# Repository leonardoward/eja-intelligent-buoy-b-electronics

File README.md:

# EJA Intelligent Buoy B with Ethernet - Electronic Design

Buoy B V2.0 integrates 4 main components (ESP32, LoRa, GPS and an Ethernet interface). It is a version of the previous Buoy B V1.0 but replaces the motor drivers with an Ethernet module.

This repository contains the KiCad design for the PCB of the Intelligent Buoy B. It also contains the 3D models used to visualize the design in the KiCad 3D viewer.

## Main Components ##

- [ESP32-DEVKITC-32D](https://www.digikey.com/product-detail/es/espressif-systems/ESP32-DEVKITC-32D/1965-1000-ND/9356990)
- [RFM95W LoRa Radio](https://www.digikey.com/product-detail/es/adafruit-industries-llc/3072/1528-1667-ND/6005357)
- [TB6612FNG MOTOR DRIVER BOARD](https://www.digikey.com/product-detail/es/sparkfun-electronics/ROB-14450/1568-1755-ND/7915576)
- [Adafruit Ethernet FeatherWing](https://www.digikey.com/en/products/detail/adafruit-industries-llc/3201/6165788)

## Schematic ##

<!-- [For a detailed explanation of the schematic visit the following log.](https://hackaday.io/project/173457/log/181832-buoy-b-v10-schematic-and-pcb-design) -->

## PCB Layout ##

## Assembly ##

Components List:

1. [ESP32-DEVKITC-32D](https://www.digikey.com/product-detail/es/espressif-systems/ESP32-DEVKITC-32D/1965-1000-ND/9356990)
2. [ETHERNET FEATHERWING](https://www.digikey.com/en/products/detail/adafruit-industries-llc/3201/6165788)
3. [CONN HDR 19POS 0.1 TIN PCB](https://www.digikey.com/product-detail/es/sullins-connector-solutions/PPTC191LFBN-RC/S7017-ND/810157)
4. [CONN HDR 9POS 0.1 GOLD PCB](https://www.digikey.com/product-detail/es/sullins-connector-solutions/PPPC091LFBN-RC/S7042-ND/810181)
5. [CONN HDR 9POS 0.1 GOLD PCB](https://www.digikey.com/product-detail/es/sullins-connector-solutions/PPPC091LFBN-RC/S7042-ND/810181)
8. PCB Buoy B V1.0
9. [CONN HDR 19POS 0.1 TIN PCB](https://www.digikey.com/product-detail/es/sullins-connector-solutions/PPTC191LFBN-RC/S7017-ND/810157)
10. [TERM BLK 2P SIDE ENT 5.08MM PCB](https://www.digikey.com/product-detail/es/on-shore-technology-inc/OSTTC022162/ED2609-ND/614558)
12. [CONN HDR 6POS 0.1 TIN PCB](https://www.digikey.com/product-detail/es/sullins-connector-solutions/PPTC061LFBN-RC/S7004-ND/810145)
13. [CONN HDR 5POS 0.1 GOLD PCB](https://www.digikey.com/product-detail/es/sullins-connector-solutions/PPTC051LFBN-RC/S6103-ND/807239)
14. [CONN HEADER VERT 3POS 2.54MM](https://www.digikey.com/product-detail/es/jst-sales-america-inc/S2B-XH-A-1-LF-SN/455-4226-ND/9961922)
15. [CONN HEADER VERT 3POS 2.54MM](https://www.digikey.com/product-detail/es/jst-sales-america-inc/S2B-XH-A-1-LF-SN/455-4226-ND/9961922)
16. [CONN HEADER R/A 3POS 2.5MM](https://www.digikey.com/product-detail/es/jst-sales-america-inc/S3B-XH-A-1-LF-SN/455-2954-ND/1556255)
17. Coin cell holder (included in [Adafruit Ultimate GPS](https://www.digikey.com/product-detail/es/adafruit-industries-llc/746/1528-1153-ND/5353613))
18. [Adafruit Ultimate GPS](https://www.digikey.com/product-detail/es/adafruit-industries-llc/746/1528-1153-ND/5353613)
19. CONN HDR 16POS 0.1 TIN PCB (included in [Adafruit Ultimate GPS](https://www.digikey.com/product-detail/es/adafruit-industries-llc/746/1528-1153-ND/5353613))
20. [RFM95W LoRa Radio](https://www.digikey.com/product-detail/es/adafruit-industries-llc/3072/1528-1667-ND/6005357)
21. CONN HEADER VERT 16POS 2.54MM (included in [RFM95W LoRa Radio](https://www.digikey.com/product-detail/es/adafruit-industries-llc/3072/1528-1667-ND/6005357))

<!-- [For a detailed Bill of Materials visit the following log.](https://hackaday.io/project/173457/log/183762-buoy-b-v10-bill-of-materials)

[For a detailed explanation about the soldering and assembly procedure visit the following log.](https://hackaday.io/project/173457/log/183666-buoy-b-v10-assembly) -->

<!-- ## Wiring Diagrams ##

### Battery Management ###

The original design of the board considered the following components:

- Battery (5V < Voltage < 15V)
- PCB Board Buoy B V1.0
- Buck Converter
- Switch
- Extra capacitor

Also, there is an alternative for the battery management, is possible to provide the required voltages with a boost converter and a 3.7V Battery, like the following example:

- 3.7V 1 Cell Battery
- PCB Board Buoy B V1.0
- Boost Converter
- Micro USB Breakout Board
- Switch
- Extra capacitor
- JST-XH 2 Pos female connector and a JST-XH 2 Pos male connector
- 5V Charger (only used to charge the battery)

This alternative is valid and possible, but is not ideal for longer working time (compared to the first one). It is important to consider the efficiency of the boost converter. The selected boost converter will have a voltage drop at a current higher than 500mA, that should be taken into consideration.

### Motors ###

The board was designed to handle 3 different types of motors, those are:

- Servo Motor

- Stepper Motor (using the driver TB6612FNG)

- DC Motor (using the driver TB6612FNG)

[For more information about the wiring diagrams and the project visit the following log.](https://hackaday.io/project/173457/log/182722-buoy-b-v10-wiring-diagrams)

## Future improvements ##

[For more information about the recommended future improvements for the electronic design visit the following log.](https://hackaday.io/project/173457/log/183807-future-improvements-pcb-design) -->

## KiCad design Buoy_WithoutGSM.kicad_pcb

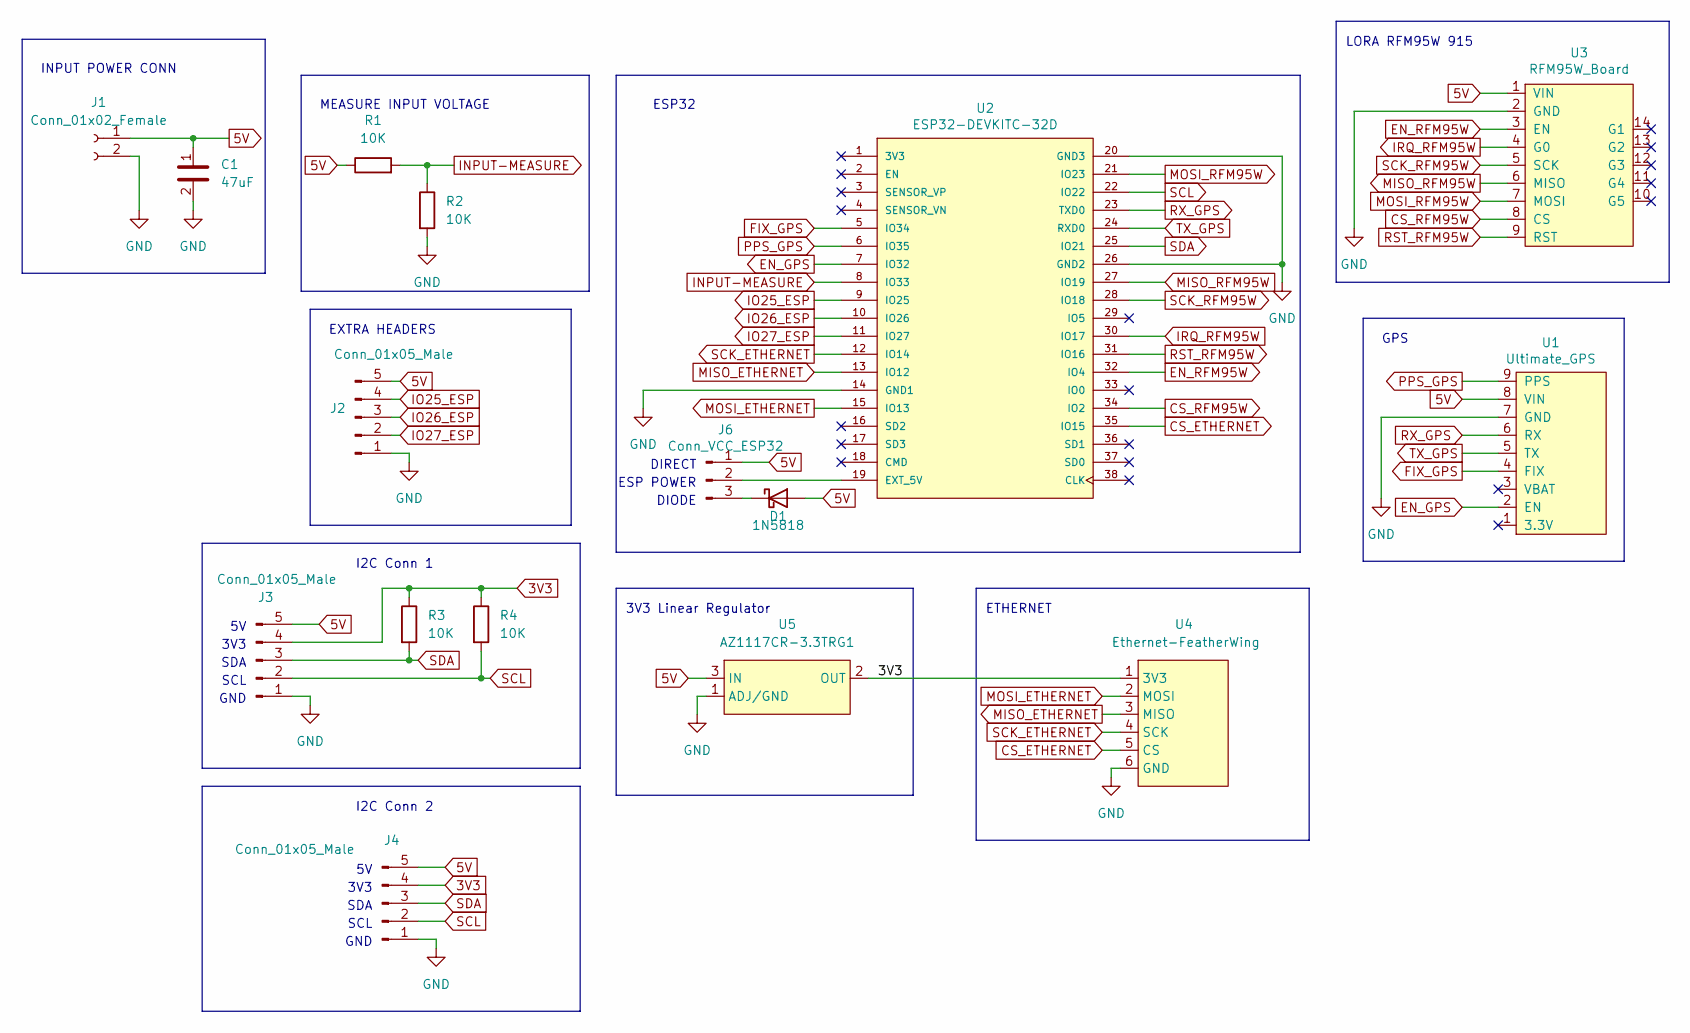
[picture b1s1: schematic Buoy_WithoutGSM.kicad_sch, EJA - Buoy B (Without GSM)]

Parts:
C1: 47uF; R_0805_2012Metric_Pad1.20x1.40mm_HandSolder; Manufacturer_Part_Number LMK212BBJ476MG-T
D1: 1N5818; D_DO-41_SOD81_P10.16mm_Horizontal
J1: Conn_01x02_Female; TerminalBlock_bornier-2_P5.08mm
J2, J3, J4: Conn_01x05_Male; PinSocket_1x05_P2.54mm_Vertical
J6: Conn_VCC_ESP32; PinHeader_1x03_P2.54mm_Vertical
R1, R2, R3, R4: 10K; R_0805_2012Metric; Manufacturer_Part_Number CRCW080510K0FKEAC
U1: Ultimate_GPS
U2: ESP32-DEVKITC-32D; MODULE_ESP32-DEVKITC-32D
U3: RFM95W_Board; RFM95W-Board
U4: Ethernet-FeatherWing; Ethernet FeatherWing; Manufacturer Part Number 3201
U5: AZ1117CR-3.3TRG1; SOT-89-3_Handsoldering; Manufacturer_Part_Name AZ1117CR-3.3TRG1

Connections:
3V3: J3.4, J4.4, R3.1, R4.1, U4.1 (3V3), U5.2 (OUT)
5V: C1.1, D1.2 (A), J1.1, J2.5, J3.5, J4.5, J6.1, R1.1, U1.8 (VIN), U3.1 (VIN), U5.3 (IN)
CS_ETHERNET: U2.35 (IO15), U4.5 (CS)
CS_RFM95W: U2.34 (IO2), U3.8 (CS)
EN_GPS: U1.2 (EN), U2.7 (IO32)
EN_RFM95W: U2.32 (IO4), U3.3 (EN)
FIX_GPS: U1.4 (FIX), U2.5 (IO34)
GND: C1.2, J1.2, J2.1, J3.1, J4.1, R2.2, U1.7 (GND), U2.14 (GND1), U2.20 (GND3), U2.26 (GND2), U3.2 (GND), U4.6 (GND), U5.1 (ADJ/GND)
INPUT-MEASURE: R1.2, R2.1, U2.8 (IO33)
IO25_ESP: J2.4, U2.9 (IO25)
IO26_ESP: J2.3, U2.10 (IO26)
IO27_ESP: J2.2, U2.11 (IO27)
IRQ_RFM95W: U2.30 (IO17), U3.4 (G0)
MISO_ETHERNET: U2.13 (IO12), U4.3 (MISO)
MISO_RFM95W: U2.27 (IO19), U3.6 (MISO)
MOSI_ETHERNET: U2.15 (IO13), U4.2 (MOSI)
MOSI_RFM95W: U2.21 (IO23), U3.7 (MOSI)
unnamed: D1.1 (K), J6.3
unnamed: J6.2, U2.19 (EXT_5V)
PPS_GPS: U1.9 (PPS), U2.6 (IO35)
RST_RFM95W: U2.31 (IO16), U3.9 (RST)
RX_GPS: U1.6 (RX), U2.23 (TXD0)
SCK_ETHERNET: U2.12 (IO14), U4.4 (SCK)
SCK_RFM95W: U2.28 (IO18), U3.5 (SCK)
SCL: J3.2, J4.2, R4.2, U2.22 (IO22)
SDA: J3.3, J4.3, R3.2, U2.25 (IO21)
TX_GPS: U1.5 (TX), U2.24 (RXD0)

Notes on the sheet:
3V3
GPS
SCL
DIODE
I2C Conn 2
MEASURE INPUT VOLTAGE
LORA RFM95W 915
ESP32
GND
ETHERNET
I2C Conn 1
ESP POWER
DIRECT
SDA
3V3 Linear Regulator
INPUT POWER CONN
EXTRA HEADERS

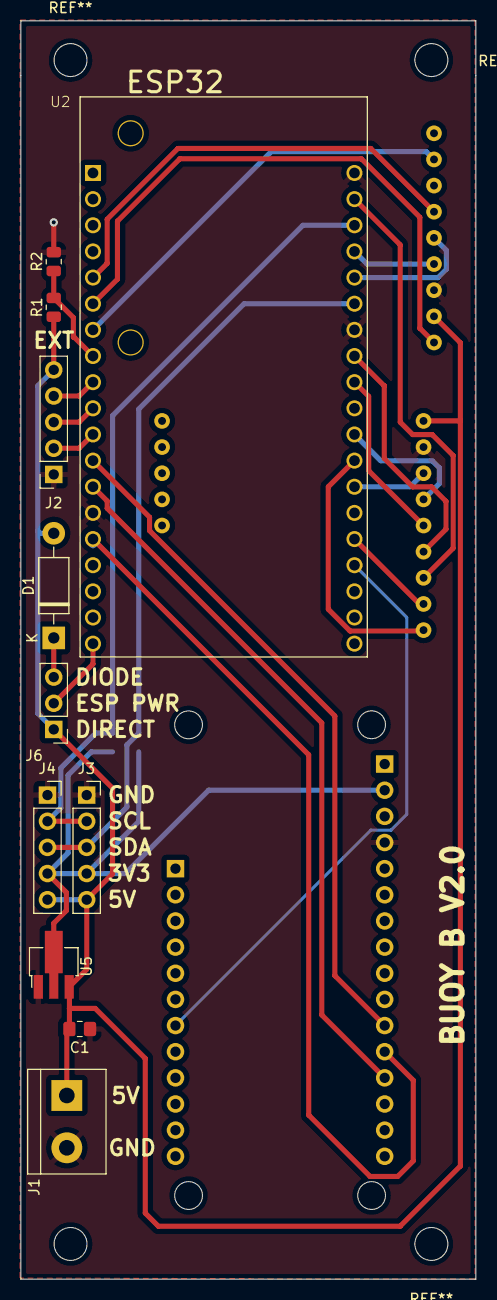
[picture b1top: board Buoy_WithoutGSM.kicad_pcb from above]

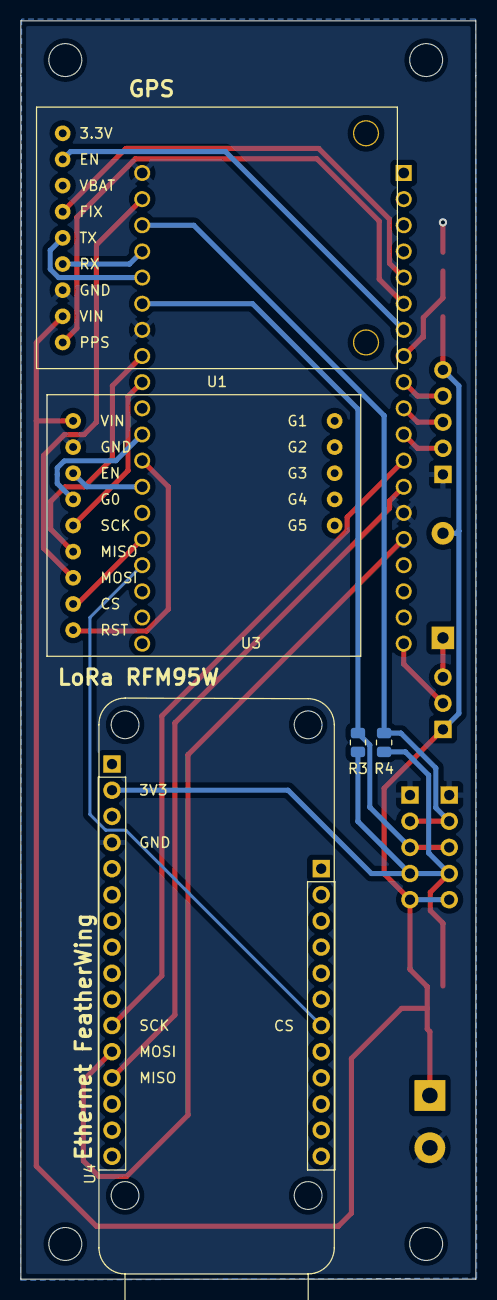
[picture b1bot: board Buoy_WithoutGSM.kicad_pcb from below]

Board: 2 copper layers, 44.2 x 122.2 mm, 16 parts (4 on the bottom side), 27 nets.

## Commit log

2020-09-28 Added KiCad design
2020-09-28 Added assembly guide and wiring diagrams
2020-09-28 Added new assembly image
2020-09-28 Fixed missing images
2020-09-28 Added components list
2020-09-28 Added links to hackaday page
2020-09-28 Fixed link to boost converter image
2020-09-28 Added future improvements
2022-08-14 Added new branch
2022-08-16 Update before modifications
2022-08-16 Updated schematic to Kicad6, removed motor diver and JST Battery connector
2022-08-16 Added Ethernet module and input measurement
2022-08-16 Added connections to the Extra Conn
2022-08-18 Added 3D model for the Ethernet module and routed changes on PCB
2022-08-19 Updated readme, added new images
2022-09-02 Changed toutes of the PCB, including routes width
2022-09-09 Updated documentation
2022-09-09 Added gerber files
2022-09-23 Moved C1 on the PCB, changed PCB shape, moved lower mounting holes
